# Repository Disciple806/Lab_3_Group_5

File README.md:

# Lab_3_Group_5
Microgrid and Power System Monitoring

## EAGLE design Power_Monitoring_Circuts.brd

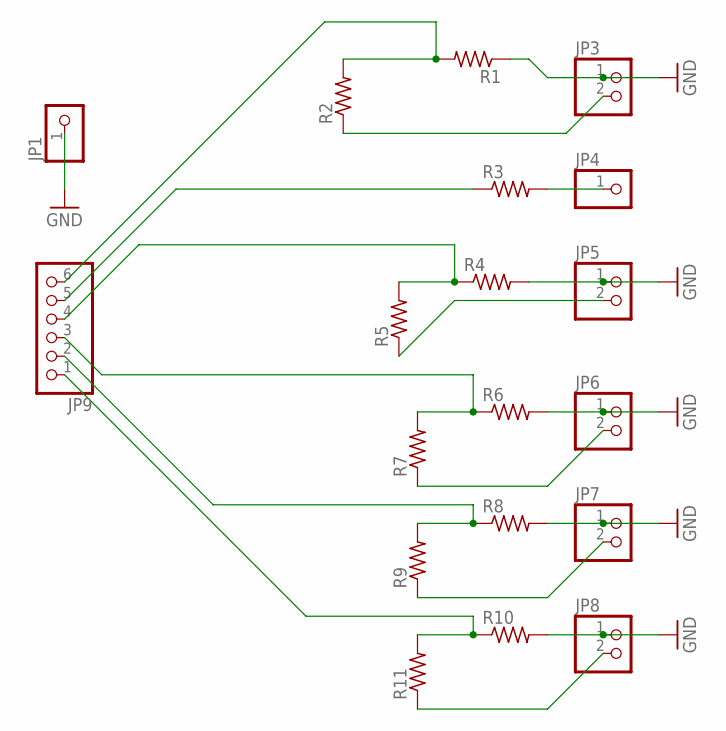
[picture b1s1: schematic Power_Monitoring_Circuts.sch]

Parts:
JP1, JP4: PINHD-1X1; 1X01
JP3, JP5, JP6, JP7, JP8: PINHD-1X2; 1X02
JP9: PINHD-1X6; 1X06
R1, R2, R3, R4, R5, R6, R7, R8, R9, R10, R11: R-US_0204/7; 0204/7

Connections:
GND: JP1.1, JP3.1, JP5.1, JP6.1, JP7.1, JP8.1, R1.1, R4.2, R6.2, R8.2, R10.2
unnamed: JP9.6, R1.2, R2.2
unnamed: JP3.2, R2.1
unnamed: JP4.1, R3.2
unnamed: JP9.4, R4.1, R5.2
unnamed: JP5.2, R5.1
unnamed: JP9.3, R6.1, R7.2
unnamed: JP6.2, R7.1
unnamed: JP9.2, R8.1, R9.2
unnamed: JP9.5, R3.1
unnamed: JP9.1, R10.1, R11.2
unnamed: JP8.2, R11.1
unnamed: JP7.2, R9.1

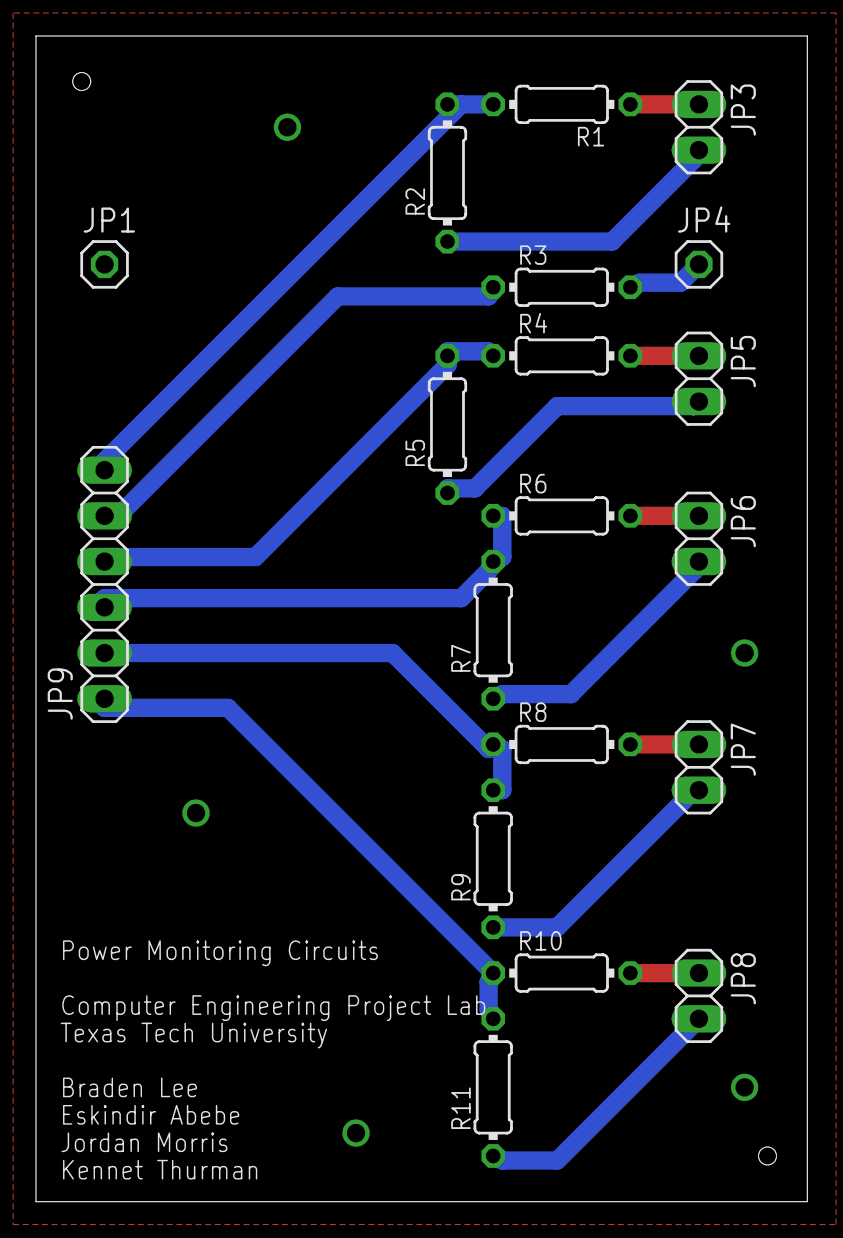
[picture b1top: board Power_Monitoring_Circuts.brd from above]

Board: 2 copper layers, 42.9 x 64.8 mm, 19 parts (0 on the bottom side), 13 nets.

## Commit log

2018-10-02 Add files via upload
    This is the library file which contains the Eagle device for the 1N5824 Diode
2018-10-17 Create MSP430_ADC
2018-10-17 Create MCP3008_Code
